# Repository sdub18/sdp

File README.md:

# Senior Design Project UMass Electrical and Computer Engineering - Team 23
Motor Health Analytics and Feedback Dashboard
Sam DuBois, Andres Gutierrez, Andrew Tran, and Michael Brauninger

Packages Necessary to Download to Run Arduino Code
- Adafruit MCP9808
- Adafruit LIS3DH
- Adafruit INA260
- ArduinoJSON6

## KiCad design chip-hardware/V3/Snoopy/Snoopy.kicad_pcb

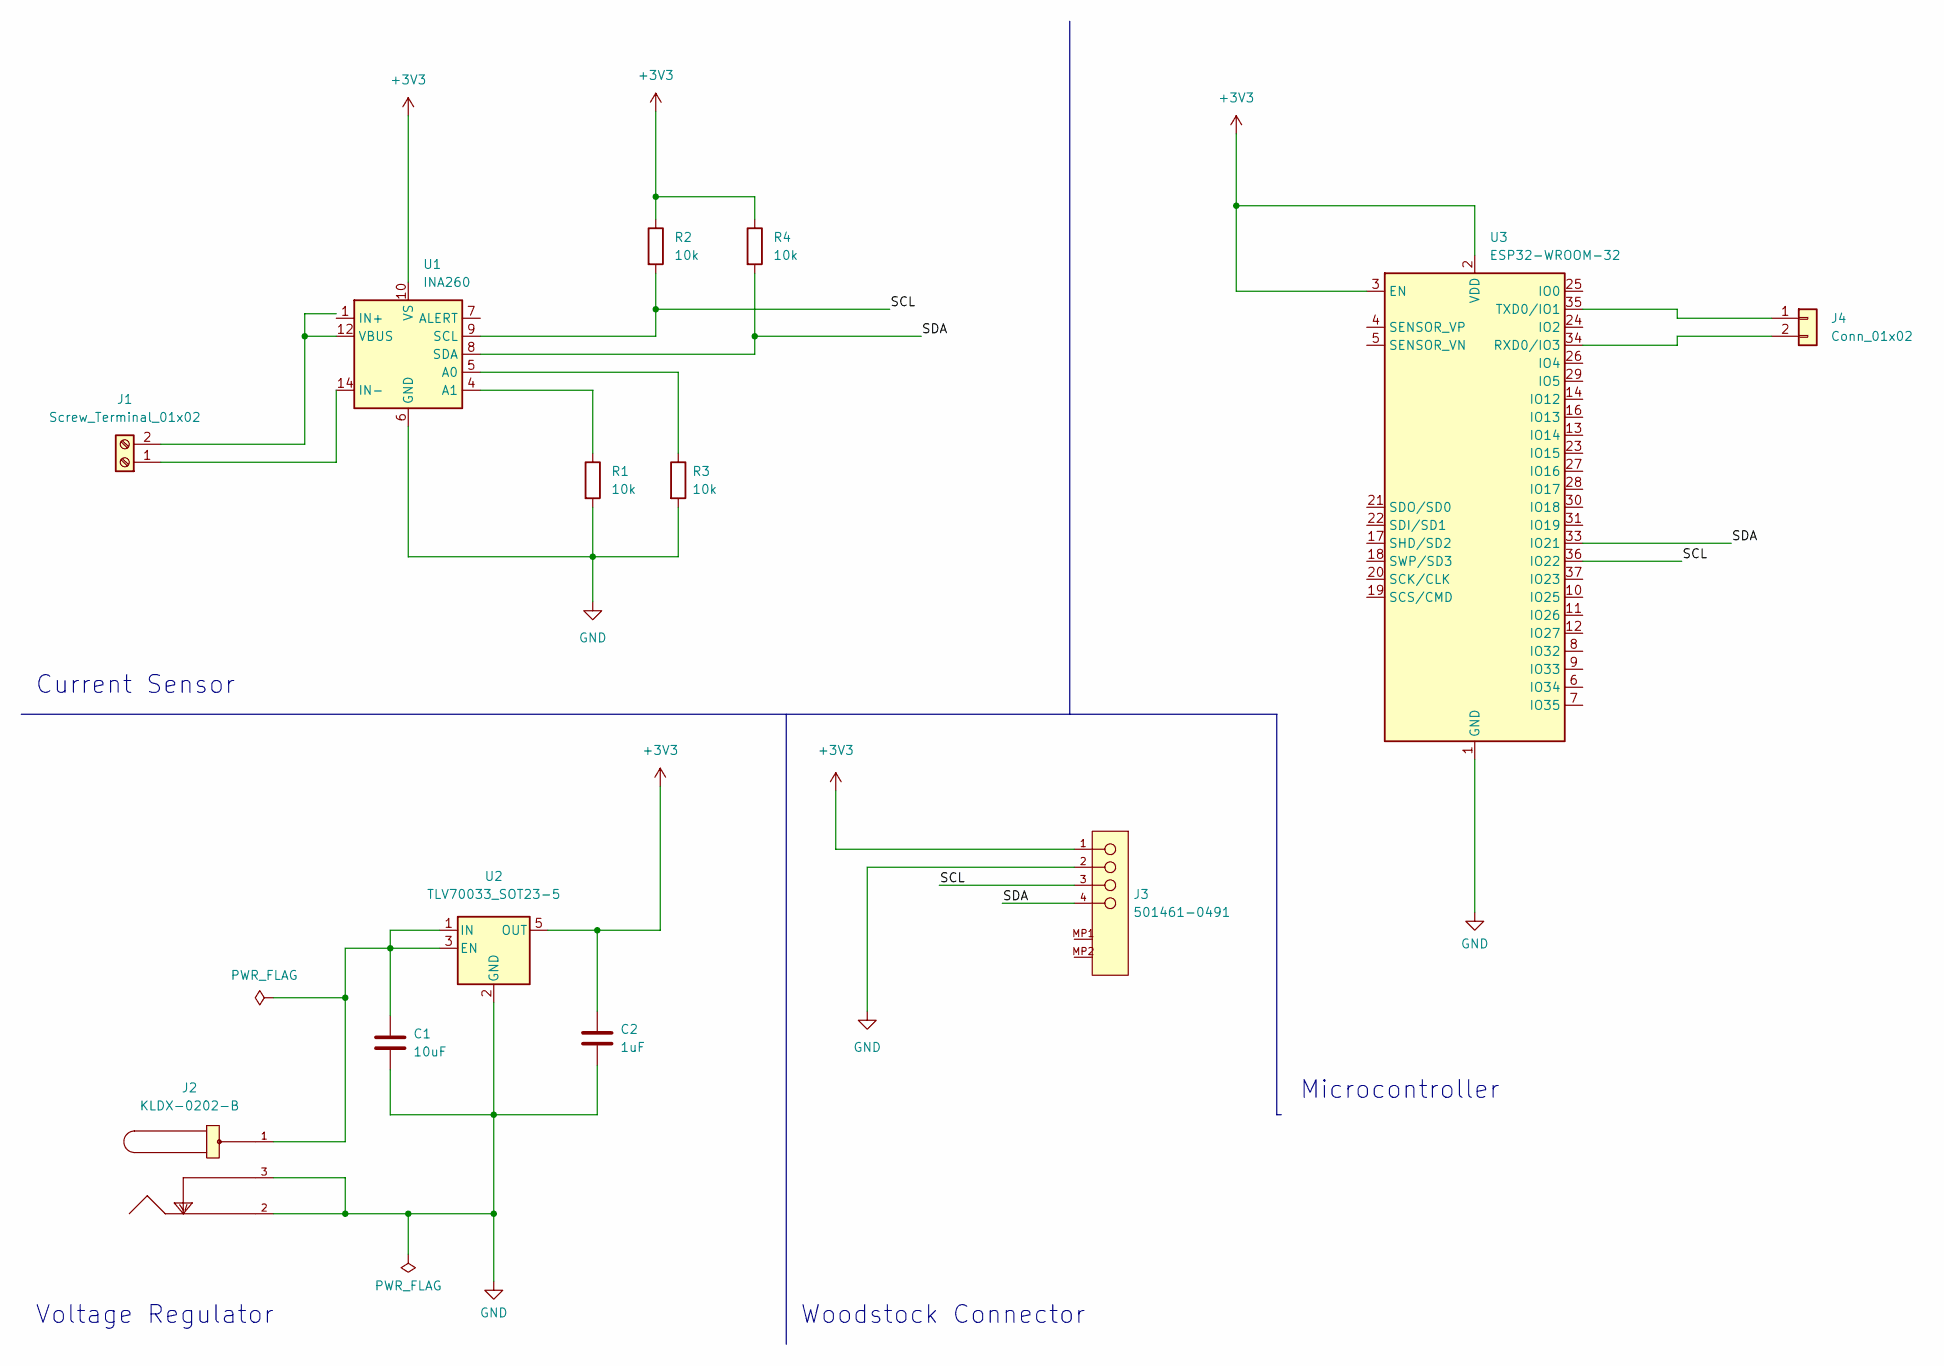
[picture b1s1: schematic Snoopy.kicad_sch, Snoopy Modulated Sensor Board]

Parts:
C1: 10uF; C_0603_1608Metric_Pad1.08x0.95mm_HandSolder
C2: 1uF; C_0603_1608Metric_Pad1.08x0.95mm_HandSolder
J1: Screw_Terminal_01x02; TerminalBlock_RND_205-00232_1x02_P5.08mm_Horizontal
J2: KLDX-0202-B; Kycon-KLDX-0202-B-MFG; current rating 3.5A; voltage rating 24V; mouser part number 806-KLDX-0202-B; digikey description CONN PWR JACK 2.5X5.5MM SOLDER
J3: 501461-0491; Molex-501461-0491-Manufacturer_Recommended; Voltage Max 50V AC (RMS)/DC
J4: Conn_01x02; SolderWire-0.1sqmm_1x02_P3.6mm_D0.4mm_OD1mm
R1, R2, R3, R4: 10k; R_0603_1608Metric_Pad0.98x0.95mm_HandSolder
U1: INA260; TSSOP-16_4.4x5mm_P0.65mm
U2: TLV70033_SOT23-5; SOT-23-5
U3: ESP32-WROOM-32

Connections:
+3V3: C2.1, J3.1, R2.1, R4.1, U1.10 (VS), U2.5 (OUT), U3.2 (VDD), U3.3 (EN)
/SCL: J3.3, R2.2, U1.9 (SCL), U3.36 (IO22)
/SDA: J3.4, R4.2, U1.8 (SDA), U3.33 (IO21)
GND: C1.2, C2.2, J2.2, J2.3, J3.2, R1.2, R3.2, U1.6 (GND), U1.11 (GND), U2.2 (GND), U3.1 (GND), U3.15 (GND), U3.38 (GND), U3.39 (GND)
unnamed: C1.1, J2.1, U2.1 (IN), U2.3 (EN)
unnamed: J1.1, U1.14 (IN-), U1.15 (IN-), U1.16 (IN-)
unnamed: J1.2, U1.12 (VBUS)
unnamed: J4.1, U3.35 (TXD0/IO1)
unnamed: J4.2, U3.34 (RXD0/IO3)
unnamed: R1.1, U1.4 (A1)
unnamed: R3.1, U1.5 (A0)
unnamed: U1.1 (IN+), U1.2 (IN+), U1.3 (IN+)

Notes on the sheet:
Voltage Regulator
Woodstock Connector
Microcontroller
Current Sensor

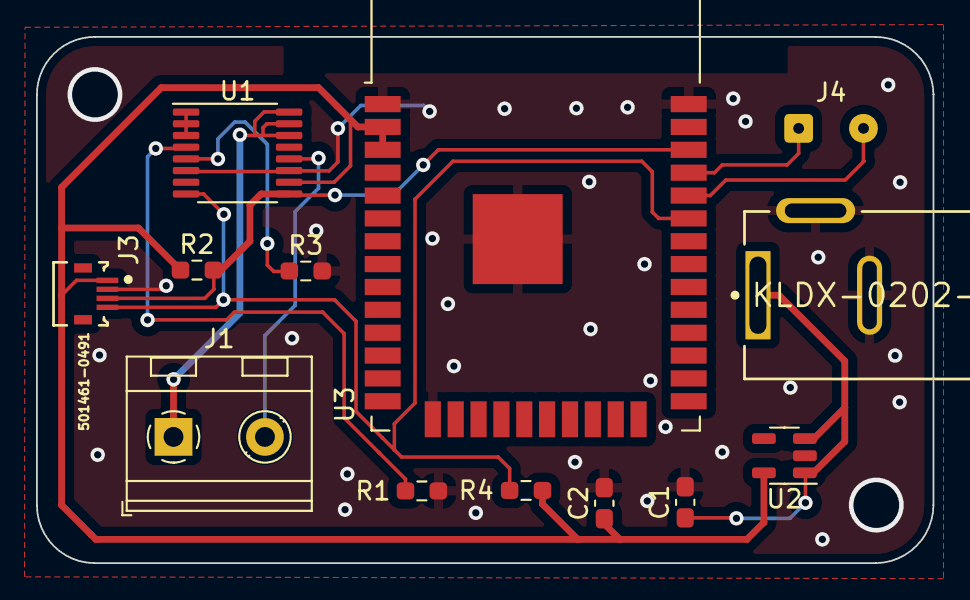
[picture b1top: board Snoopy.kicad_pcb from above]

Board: 2 copper layers, 49.8 x 29.2 mm, 13 parts (0 on the bottom side), 12 nets.

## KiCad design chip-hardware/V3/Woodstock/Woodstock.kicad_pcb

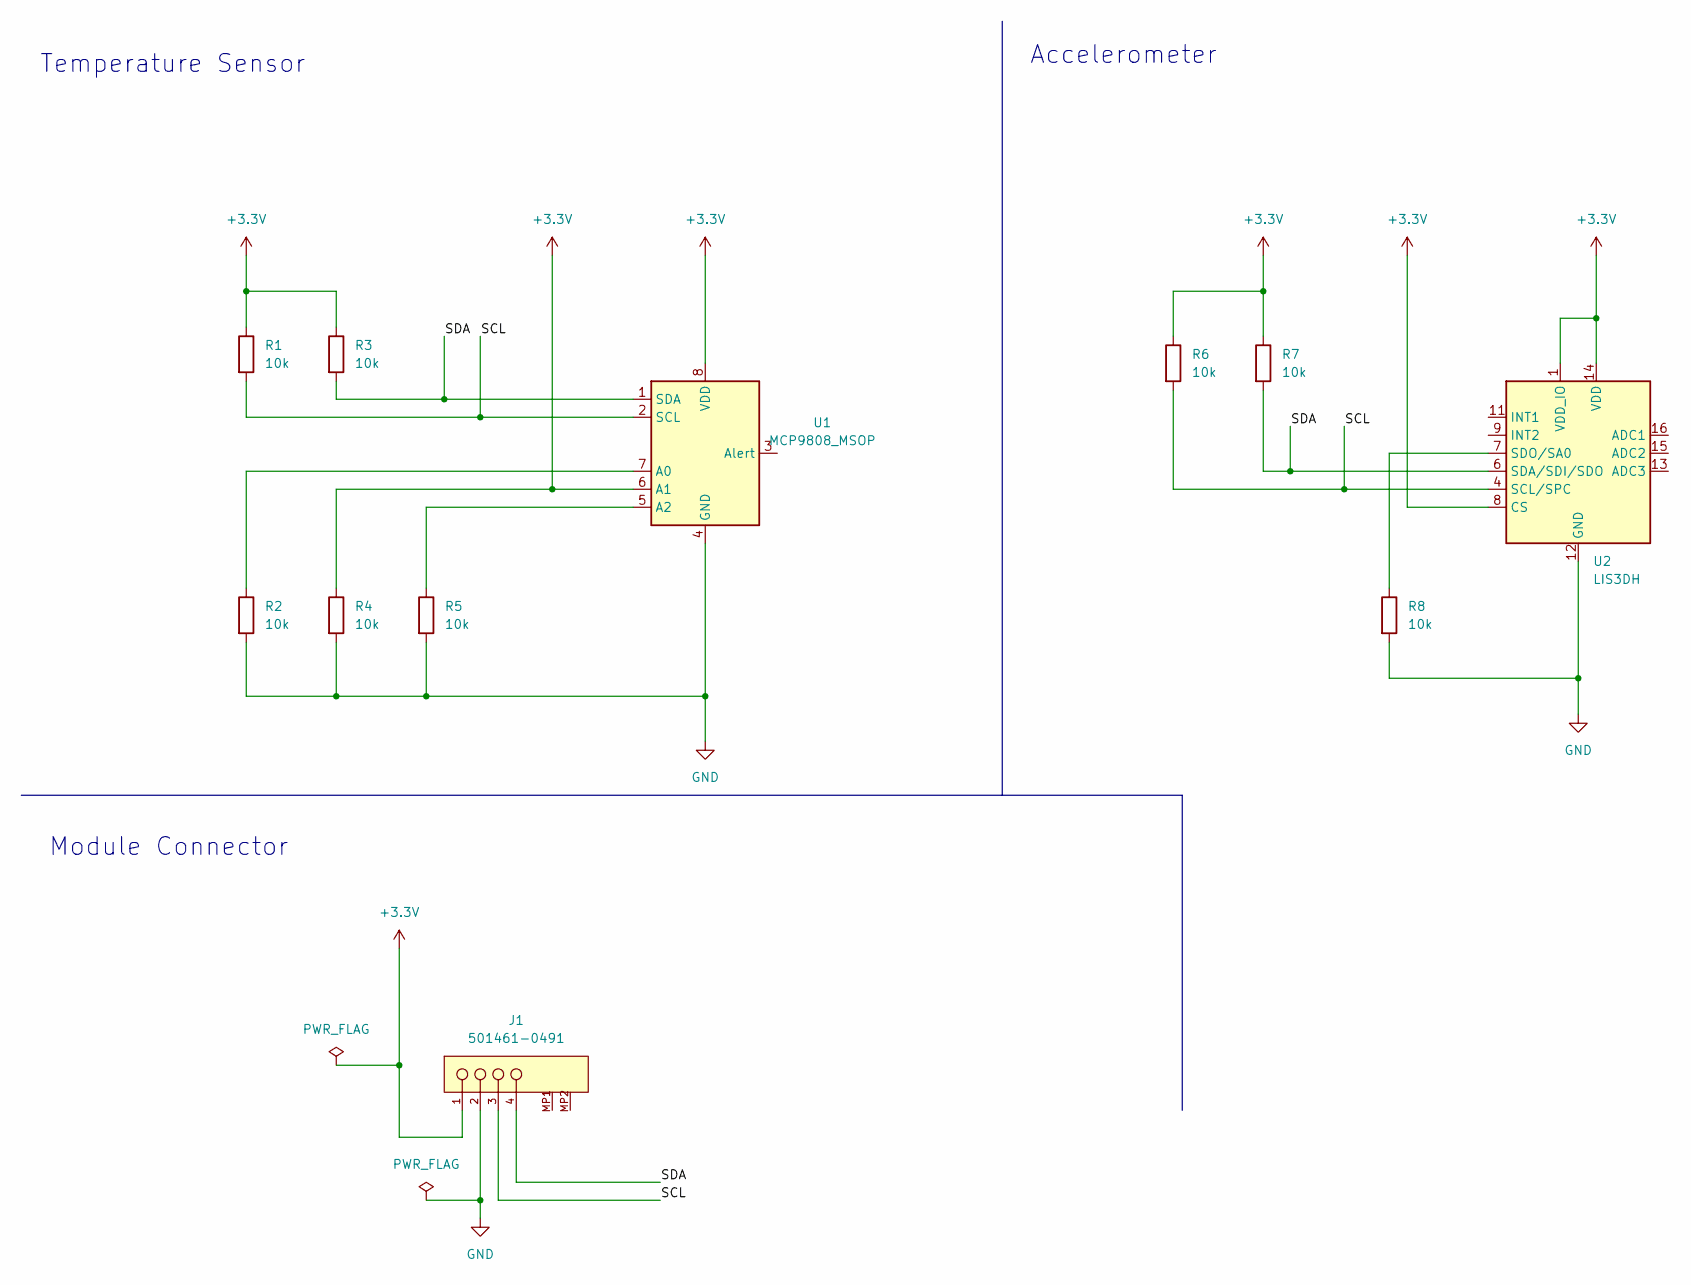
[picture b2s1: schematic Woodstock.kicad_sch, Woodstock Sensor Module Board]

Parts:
J1: 501461-0491; Molex-501461-0491-Manufacturer_Recommended; Voltage Max 50V AC (RMS)/DC
R1, R2, R3, R4, R5, R6, R7, R8: 10k; R_0603_1608Metric_Pad0.98x0.95mm_HandSolder
U1: MCP9808_MSOP; MSOP-8_3x3mm_P0.65mm
U2: LIS3DH; LGA-16_3x3mm_P0.5mm_LayoutBorder3x5y

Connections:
+3V3: J1.1, R1.1, R3.1, R4.1, R6.1, R7.1, U1.6 (A1), U1.8 (VDD), U2.1 (VDD_IO), U2.8 (CS), U2.14 (VDD)
/SCL: J1.3, R1.2, R6.2, U1.2 (SCL), U2.4 (SCL/SPC)
/SDA: J1.4, R3.2, R7.2, U1.1 (SDA), U2.6 (SDA/SDI/SDO)
GND: J1.2, R2.2, R4.2, R5.2, R8.2, U1.4 (GND), U2.5 (GND), U2.10 (GND), U2.12 (GND)
unnamed: R2.1, U1.7 (A0)
unnamed: R5.1, U1.5 (A2)
unnamed: R8.1, U2.7 (SDO/SA0)

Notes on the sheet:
Module Connector
Temperature Sensor
Accelerometer

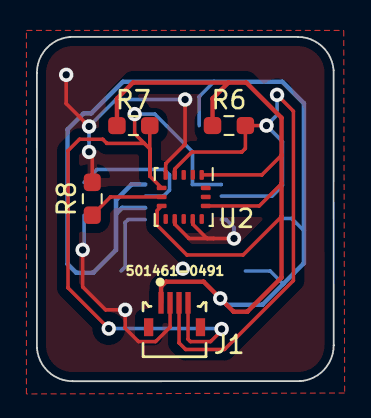
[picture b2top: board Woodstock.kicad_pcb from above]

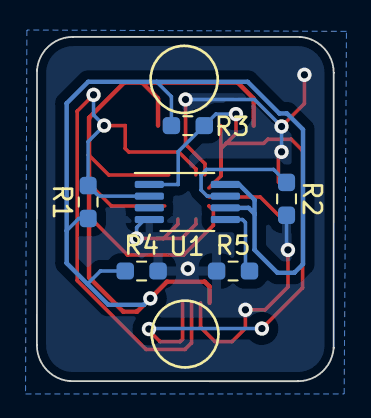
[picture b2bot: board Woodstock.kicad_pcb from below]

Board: 2 copper layers, 16.5 x 19.1 mm, 11 parts (6 on the bottom side), 7 nets.

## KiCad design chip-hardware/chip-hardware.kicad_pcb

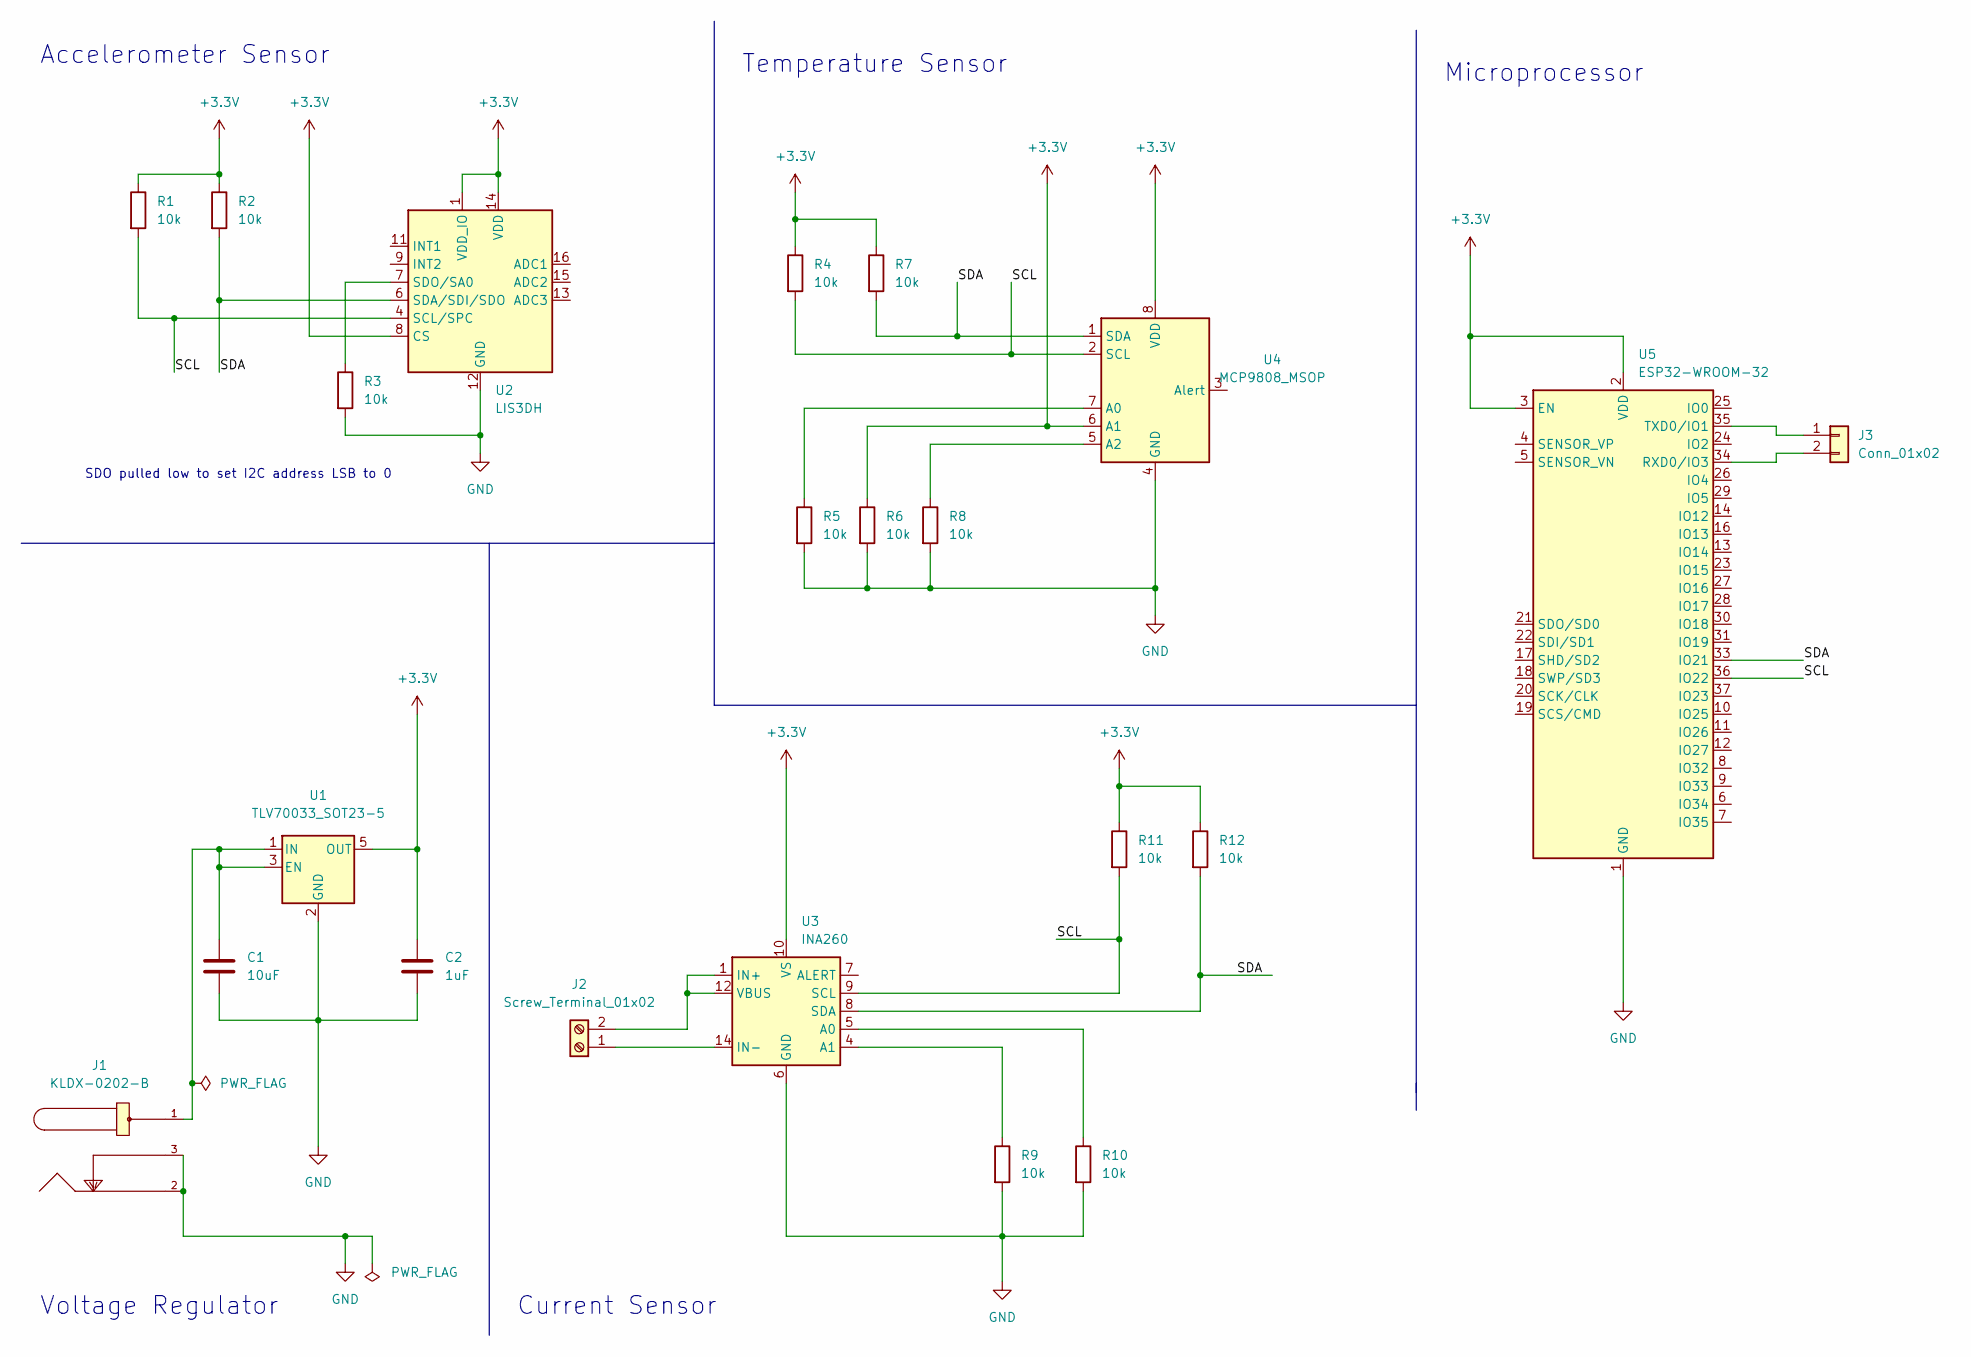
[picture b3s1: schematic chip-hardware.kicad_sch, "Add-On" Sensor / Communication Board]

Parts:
C1: 10uF; C_0603_1608Metric_Pad1.08x0.95mm_HandSolder
C2: 1uF; C_0603_1608Metric_Pad1.08x0.95mm_HandSolder
J1: KLDX-0202-B; Kycon-KLDX-0202-B-MFG; current rating 3.5A; voltage rating 24V; mouser part number 806-KLDX-0202-B; digikey description CONN PWR JACK 2.5X5.5MM SOLDER
J2: Screw_Terminal_01x02; TerminalBlock_RND_205-00232_1x02_P5.08mm_Horizontal
J3: Conn_01x02; SolderWire-0.1sqmm_1x02_P3.6mm_D0.4mm_OD1mm
R1, R2, R3, R4, R5, R6, R7, R8, R9, R10, R11, R12: 10k; R_0603_1608Metric_Pad0.98x0.95mm_HandSolder
U1: TLV70033_SOT23-5; SOT-23-5
U2: LIS3DH; LGA-16_3x3mm_P0.5mm_LayoutBorder3x5y
U3: INA260; TSSOP-16_4.4x5mm_P0.65mm
U4: MCP9808_MSOP; MSOP-8_3x3mm_P0.65mm
U5: ESP32-WROOM-32

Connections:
+3V3: C2.1, R1.1, R2.1, R4.1, R6.1, R7.1, R11.1, R12.1, U1.5 (OUT), U2.1 (VDD_IO), U2.8 (CS), U2.14 (VDD), U3.10 (VS), U4.6 (A1), U4.8 (VDD), U5.2 (VDD), U5.3 (EN)
/SCL: R1.2, R4.2, R11.2, U2.4 (SCL/SPC), U3.9 (SCL), U4.2 (SCL), U5.36 (IO22)
/SDA: R2.2, R7.2, R12.2, U2.6 (SDA/SDI/SDO), U3.8 (SDA), U4.1 (SDA), U5.33 (IO21)
GND: C1.2, C2.2, J1.2, J1.3, R3.2, R5.2, R6.2, R8.2, R9.2, R10.2, U1.2 (GND), U2.5 (GND), U2.10 (GND), U2.12 (GND), U3.6 (GND), U3.11 (GND), U4.4 (GND), U5.1 (GND), U5.15 (GND), U5.38 (GND), U5.39 (GND)
unnamed: C1.1, J1.1, U1.1 (IN), U1.3 (EN)
unnamed: J2.1, U3.14 (IN-), U3.15 (IN-), U3.16 (IN-)
unnamed: J2.2, U3.1 (IN+), U3.2 (IN+), U3.3 (IN+), U3.12 (VBUS)
unnamed: J3.1, U5.35 (TXD0/IO1)
unnamed: J3.2, U5.34 (RXD0/IO3)
unnamed: R3.1, U2.7 (SDO/SA0)
unnamed: R5.1, U4.7 (A0)
unnamed: R8.1, U4.5 (A2)
unnamed: R9.1, U3.4 (A1)
unnamed: R10.1, U3.5 (A0)

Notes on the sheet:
Current Sensor
Temperature Sensor
Microprocessor
Accelerometer Sensor
Voltage Regulator
SDO pulled low to set I2C address LSB to 0

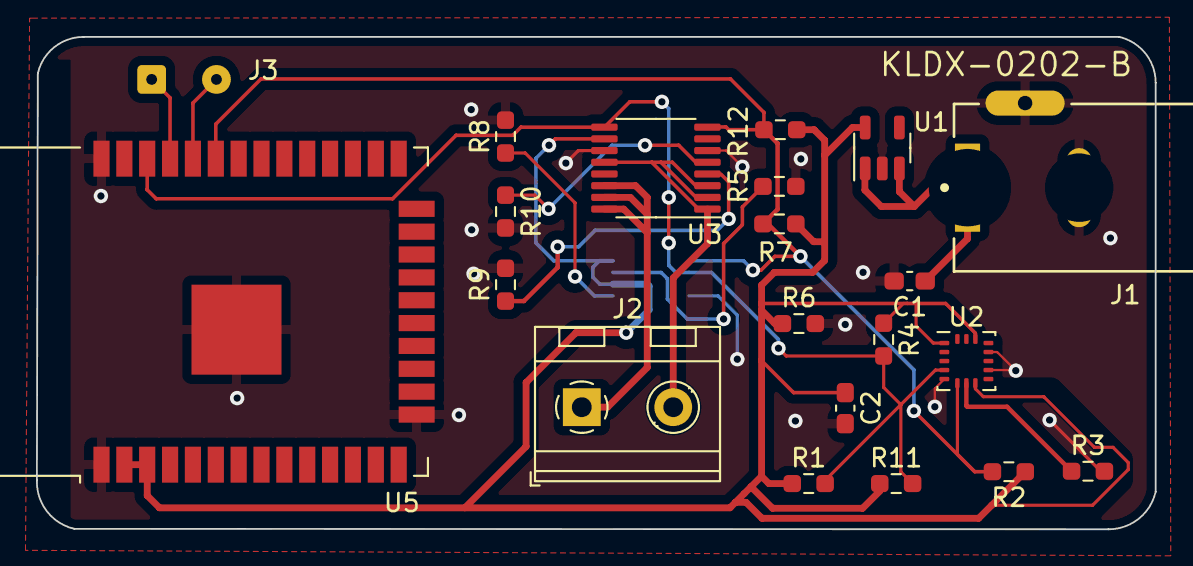
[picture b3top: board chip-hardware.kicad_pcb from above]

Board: 2 copper layers, 62.2 x 27.4 mm, 22 parts (1 on the bottom side), 14 nets.

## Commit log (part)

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2021-10-17 initialized i2c files
2021-11-07 Basic frontend and server
2021-11-07 Fixing git issue
2021-11-07 Added basic graph and Material UI
2021-11-09 initialized backend
2021-11-09 added client limit on server for testing
2021-11-09 handles client connection closing
2021-11-10 server.js can accept from any address + comments
2021-11-10 TCP client code for sensorboard
2021-11-11 added pthread.h for sensorboard client file
2021-11-11 moved folders to frontend for less confusion
2021-11-12 installed ws package
2021-11-13 Adding websocket package and requirements
2021-11-13 Changed HTTP requests to websocket for live-data
2021-11-14 Receive multiple values (JSON) not just single int
2021-11-17 Edited data fromatting
2021-11-21 comments and restructuring for organization
2021-11-21 init commit
2021-11-21 ambient temp working with current
2021-11-22 variable chart design
2021-11-22 include acceleration values in data packet
2021-11-22 removed unneeded variables
2021-11-22 comments?
2021-11-22 Functioning graphmenu component
2021-11-22 added gmenu component to choose displayed chart
2021-11-22 created dropdown component for selecting addons
2021-11-22 comments on buttons/dropdown components
2021-11-22 Commented server code
2021-11-23 Implemented middleman graph infrastructure
2021-11-23 cleaned up conditionals for choosing data to send
2021-11-23 config object to easily change chart props
2021-11-24 Only update y in coordinates instead of x and y
2021-11-24 combined both M2F socket on connection handlers
2021-11-24 fixed M2F onConn mistake from prev commit + clean
2021-11-24 forgot to add changes from last commit rip
2021-11-24 this is not even a real commit wtf
2021-11-24 moved server to backend directory
2021-11-25 manage new addons
2021-11-25 handle addition and removal of addons
2021-11-25 Changed AddonDropdown title
2021-11-25 Implemented addon selectability
2021-11-25 data sent IFF selected id matches incoming data id
2021-11-25 frontend looks
2021-11-27 update parseData to not use custom start/end
2021-11-27 client_sim networking --> esp32 firmware
2021-11-28 optimizing frontend performance: memo components
2021-11-28 removed denque
2021-11-28 rerender timing no longer dependent on middleman
2021-11-28 only update addons state when one is added/removed
2021-11-28 Potentially helpful circuit python libraries
2021-11-28 added .gitignore because npm is annoying as fuck
2021-11-28 gitignore pt2
2021-11-28 Added code to get current sensor working
2021-11-28 Added code for accelerometer, temp sensor, and the combination of them both
2021-11-28 Added accelerometer isolated test
2021-11-28 Got all sensors working together
2021-11-29 sendFreq parameter for ESP32 data transmission
2021-11-29 removed unnecessary rerender of dropdown component
2021-11-29 restructure code; handle bottlenecking issues
2021-11-29 updated comments
2021-11-29 Included PID in simulated client
2021-11-30 Added basic healthy/danger visualization
2021-12-01 some esp32 code
2021-12-02 Created AttributeList
2021-12-02 removed header/trailer from packet; not needed
2021-12-02 added header/trailed change to main sim
2021-12-02 Made sine wave simulated client for demo
2021-12-02 Added simulated client triangle wave for demo
2021-12-02 Got UART communication working between raspberry pi and teensy
2021-12-02 updated gitignore
2021-12-02 Finished up the beggining of the MDR code
2021-12-02 More changes to the MDR script
2021-12-02 Resolved small bugs with code. Ran tests and works great
2021-12-02 Revert "updated data packet"
    This reverts commit c32710525fb463adf0c45e6f68bebcc438b97b8e.
2021-12-02 Axis adjustment, json reformatting
2021-12-03 Style updates
2022-02-10 init
2022-02-10 connected physical system to display system
2022-02-10 cleaned up code
2022-02-10 cleaned up rpi code
2022-02-16 Bug fixes for issues related to multiple processes and frontend setup
2022-02-19 removed unnecessary node modules
2022-02-19 reverted to old .gitignore
2022-02-19 remove all instances of node_modules
2022-02-20 include package.json for backend
2022-03-03 Update addon list only upon process instantiation or termination
2022-03-05 organize old code
2022-03-05 esp32 code upload
2022-03-05 update platformio (arduino) dependencies
2022-03-08 Moved main computation away from frontend and to server
2022-03-08 Update to get everything on-track for moving frontend computation to backend
2022-03-09 hardware integration init fixes
2022-03-10 install nodemon dependency in backend
2022-03-10 Adjusted simulated demo clients for new infrastructure
2022-03-10 Made frontend health monitor component
2022-03-10 dynamically choose y axes ranges
2022-03-10 minimum range check
2022-03-11 bug fix: adding/removing addons resets page
2022-03-11 Setup live health status monitor
2022-03-11 auto set y axes
2022-03-11 clean up server code; helpers to utils folder
2022-03-11 forgot a config parameter for createGraph function
2022-03-11 Presentation stuff
2022-03-13 file name change
2022-03-13 Added initial main chips to the sch
2022-03-14 Added More components and wired up Accelerometer
2022-03-14 Got temperature sensor working
2022-03-15 finished schematic drawing. Everything is looking really good so far
2022-03-15 Annotated all of the components. Everything looking good so far
2022-03-15 Made a small positional change
2022-03-15 Trying to remove warnings from chip
2022-03-18 Added actual part associations for PCB, started work on PCB
2022-03-18 Added corner radius to the chip
2022-03-18 pulled in pretty format for new barrel jack connector
2022-03-18 Got the traces mostly done. Just need to do some reviewing
2022-03-18 filled the zones
2022-03-18 fixing some buggs
2022-03-18 wired in all connecitions. Everything is looking good
2022-03-19 Circuit has no errors and looks good. Think it may be ready for submission
2022-03-19 Added changes to the pcb to fix some small layout issues with the LIS3DH chip
2022-03-19 filled out page settings
2022-03-19 started working on the second iteration of the schematic
2022-03-19 Added pwr flag
2022-03-19 All parts associated correctly and assigned to parts
2022-03-19 edge cuts introduced
2022-03-19 Front traces added onto board
2022-03-19 Added traces to the back.
2022-03-19 Adjusted the PCB and fixed some errors with one of the chips
2022-03-19 fixed all errors and removed all warnings
2022-03-19 placed some additional ias
2022-03-19 Added the inital components to snoopy
2022-03-19 Got the rest of the parts worked out
2022-03-19 Added pages settings
2022-03-19 Started adding peices onto pcb
2022-03-19 Added adjustment to the PCB. Everything seems right
2022-03-19 finished second board with some minor errors
2022-03-21 Created gerber files for all our parts so they can be uploaded to jlcpcb
2022-03-22 Added all the drill files and got everything fixced
2022-03-23 Created groud planes and fixed power jack issues. Issued new gerbers for both relevant files
2022-03-24 some hardware changes and the addition of the backend into the system
2022-04-04 Created app header, updated css
2022-04-04 Move components to component folder
2022-04-04 fixed warning: key prop for list elements
2022-04-04 styling remodel
2022-04-04 made borders larger
2022-04-04 Made text and selector inline
2022-04-05 Added period selection and made dropdown more robust
2022-04-05 Component name change
2022-04-05 Fix tempConfig lines
2022-04-05 remove react-router-dom dependency
2022-04-05 removed unused styling
2022-04-05 Implement viewing logic for policy/chartviewers
2022-04-05 policyveiwer formatting
2022-04-06 added trash button icon on policy component
2022-04-06 move client simulations into folder
2022-04-06 update npm scripts
2022-04-06 INSERT functionality into DB
2022-04-06 remove db.sqlite from repo
2022-04-06 delete+recreate db file on startup
2022-04-06 install FFT dependency
2022-04-06 fix data packet structure on firmware
2022-04-06 fix client_demo_sin data packet
2022-04-06 create freq table
2022-04-06 retreive acceleration data
2022-04-06 implement fft to view frequency domain
2022-04-07 start script
2022-04-09 implement policy viewer
2022-04-09 memoize policy viewer -> increase performance
2022-04-09 Separate second view into 2 parts to select addon
2022-04-09 make id column larger so sort arrow fits
2022-04-09 add config file
2022-04-09 Implement Policy Modal to save space on main view
2022-04-09 update props callback names
2022-04-09 prepare policy components for backend integration
2022-04-09 spacing
2022-04-10 memoized health monitor
2022-04-10 integrate frontend and backend policy handling
2022-04-10 implement props destructing for readability
2022-04-11 fix vertical overflow when displaying chartviewer
2022-04-12 simplified viewPolicy callback
2022-04-12 fixed socket rerender bottleneck -> still slow
2022-04-12 theme formatting
2022-04-12 made separate smaller components
2022-04-12 implement new button compopnents
2022-04-12 import cleanup
2022-04-12 fixed backend bottleneck -> db insert
2022-04-12 implement policy updating for policyViewer
2022-04-12 folder struct reorg: containers/components/context
2022-04-12 normalize server socket event names
2022-04-12 update HealthMonitor to fit socket context changes
2022-04-12 implement insert transaction to handle bottleneck
2022-04-12 naming conflict in chooseAddon onClick handler
2022-04-13 Decompose selection component
2022-04-13 change data_types request to http
2022-04-18 Fix merge fuckup
2022-04-18 add timestamp functionality to sensor boards
2022-04-18 update INSERT -> use timestamp from sensing board
2022-04-19 Fix column headers on policy table
2022-04-19 Fix insertNewPolicy issue
2022-04-19 remove fft dependencies/functionality
2022-04-19 chartperiodselector to use state instead of red
2022-04-19 update firmware to include message delim
2022-04-19 move default chart type info to config file
2022-04-20 create period context provider
2022-04-20 remove source map in build
2022-04-20 update moduleID key to match db
2022-04-20 remove config received by socket
2022-04-20 implement text alerts
2022-04-20 implement graph period change
2022-04-20 remove credentials from github
2022-04-20 Fixed bug in computeHealthStatuses
2022-04-21 update policy creation modal, remove period
2022-04-21 remove period from policy
2022-04-21 update policy components to use restful api
2022-04-21 remove old files
2022-04-21 update all client sims
2022-04-21 change chart period dropdown to slider
2022-04-21 update data table column: id -> moduleID
2022-04-21 get data within last period
2022-04-21 update config: chartTypes -> dataTypes
2022-04-21 implement resampling on period change
2022-04-22 Pushing up new file for running the esp code through arduino instead of platform.io
2022-04-22 Upgraded code for messages
2022-04-22 Commented out testing code
2022-04-22 period selection changes samplerate in module
2022-04-22 update server so sampleRate sent to modules
2022-04-22 update client sim to handle resample
2022-04-22 sends sampleperiod to sensing modules
2022-04-23 change selected module on click of Health Monitor
2022-04-23 change units
2022-04-23 Chart update - titles, width, units
2022-04-24 phone input for user input component
2022-04-24 implmement phone number end point
2022-04-24 units
2022-04-26 Units for policy viewer
2022-04-27 folder restructure
2022-04-27 init decoupling logic in main server file
2022-04-27 Revised structure of unit labels
2022-04-27 fix voltage units
2022-04-27 Removed x axis ticks
2022-04-27 Actually remove x axis ticks
2022-04-30 update C2M disconnect messages
2022-04-30 fix healthmonitor height
2022-04-30 "policy" -> "rule"
2022-04-30 update emit events, readability
2022-04-30 implement nearest-neighbor upsample algorithm
2022-04-30 implement upsampling on decreasing timeframe
2022-04-30 rename "graph period" to timeframe
2022-04-30 update run script
2022-04-30 update main view heights for electron app
2022-05-01 temp app name
2022-05-01 update logo images
2022-05-01 update app container heights b/c electron frame
2022-05-01 init navbar implementation
